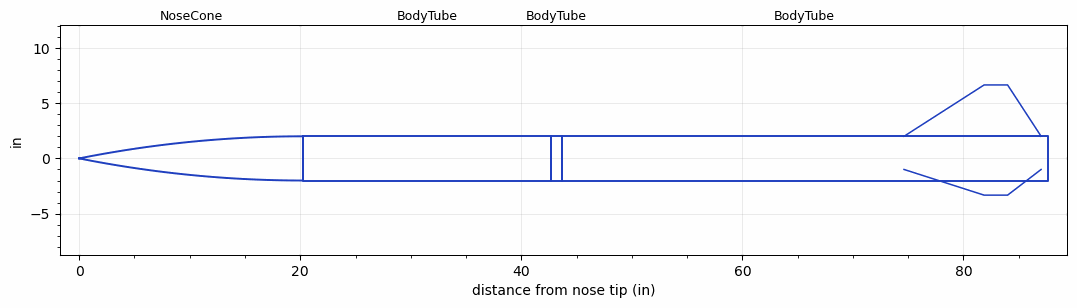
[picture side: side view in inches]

<RASAeroDocument>
 <FileVersion>2</FileVersion>
 <RocketDesign>
  <NoseCone>
   <Length>20.25</Length>
   <Diameter>4</Diameter>
   <Shape>Tangent Ogive</Shape>
   <Location>0</Location>
  </NoseCone>
  <BodyTube>
   <Length>22.40158</Length>
   <Diameter>4</Diameter>
   <Location>20.25</Location>
  </BodyTube>
  <BodyTube>
   <Length>0.984252</Length>
   <Diameter>4</Diameter>
   <Location>42.65157</Location>
  </BodyTube>
  <BodyTube>
   <Length>44</Length>
   <Diameter>4</Diameter>
   <Location>43.63583</Location>
   <Fin>
    <Count>3</Count>
    <Chord>12.40158</Chord>
    <Span>4.645669</Span>
    <SweepDistance>7.244094</SweepDistance>
    <TipChord>2.125984</TipChord>
    <Thickness>0.1181102</Thickness>
    <Location>13.01575</Location>
    <AirfoilSection>Square</AirfoilSection>
   </Fin>
  </BodyTube>
  <Surface>Smooth Paint</Surface>
  <ModifiedBarrowman>False</ModifiedBarrowman>
  <Turbulence>False</Turbulence>
  <UseBooster1>False</UseBooster1>
  <UseBooster2>False</UseBooster2>
 </RocketDesign>
 <LaunchSite>
  <Altitude>1000</Altitude>
  <Pressure>0</Pressure>
  <RodAngle>0</RodAngle>
  <RodLength>6</RodLength>
  <Temperature>74</Temperature>
  <WindSpeed>0</WindSpeed>
 </LaunchSite>
 <Recovery>
  <Altitude1>1000</Altitude1>
  <Altitude2>1000</Altitude2>
  <DeviceType1>Parachute</DeviceType1>
  <DeviceType2>None</DeviceType2>
  <Event1>True</Event1>
  <Event2>False</Event2>
  <Size1>36</Size1>
  <Size2>1</Size2>
  <EventType1>Apogee</EventType1>
  <EventType2>None</EventType2>
  <CD1>1.33</CD1>
  <CD2>1.33</CD2>
 </Recovery>
 <SimulationList>
  <Simulation>
   <SustainerEngine>L800	75	486	0	1.79	3.51	CTI  (L800	75	486	0	1.79	3.51	CTI)</SustainerEngine>
   <SustainerLaunchWt>12</SustainerLaunchWt>
   <SustainerNozzleDiameter>2.2</SustainerNozzleDiameter>
   <SustainerCG>64.5</SustainerCG>
   <SustainerIgnitionDelay>0</SustainerIgnitionDelay>
   <Booster1SeparationDelay>0</Booster1SeparationDelay>
   <Booster1IgnitionDelay>0</Booster1IgnitionDelay>
   <IncludeBooster1>False</IncludeBooster1>
   <Booster2Delay>0</Booster2Delay>
   <IncludeBooster2>False</IncludeBooster2>
   <TimetoApogee>25.76049</TimetoApogee>
   <MaxAltitude>14112.3</MaxAltitude>
   <MaxVelocity>1455.817</MaxVelocity>
  </Simulation>
 </SimulationList>
</RASAeroDocument>
